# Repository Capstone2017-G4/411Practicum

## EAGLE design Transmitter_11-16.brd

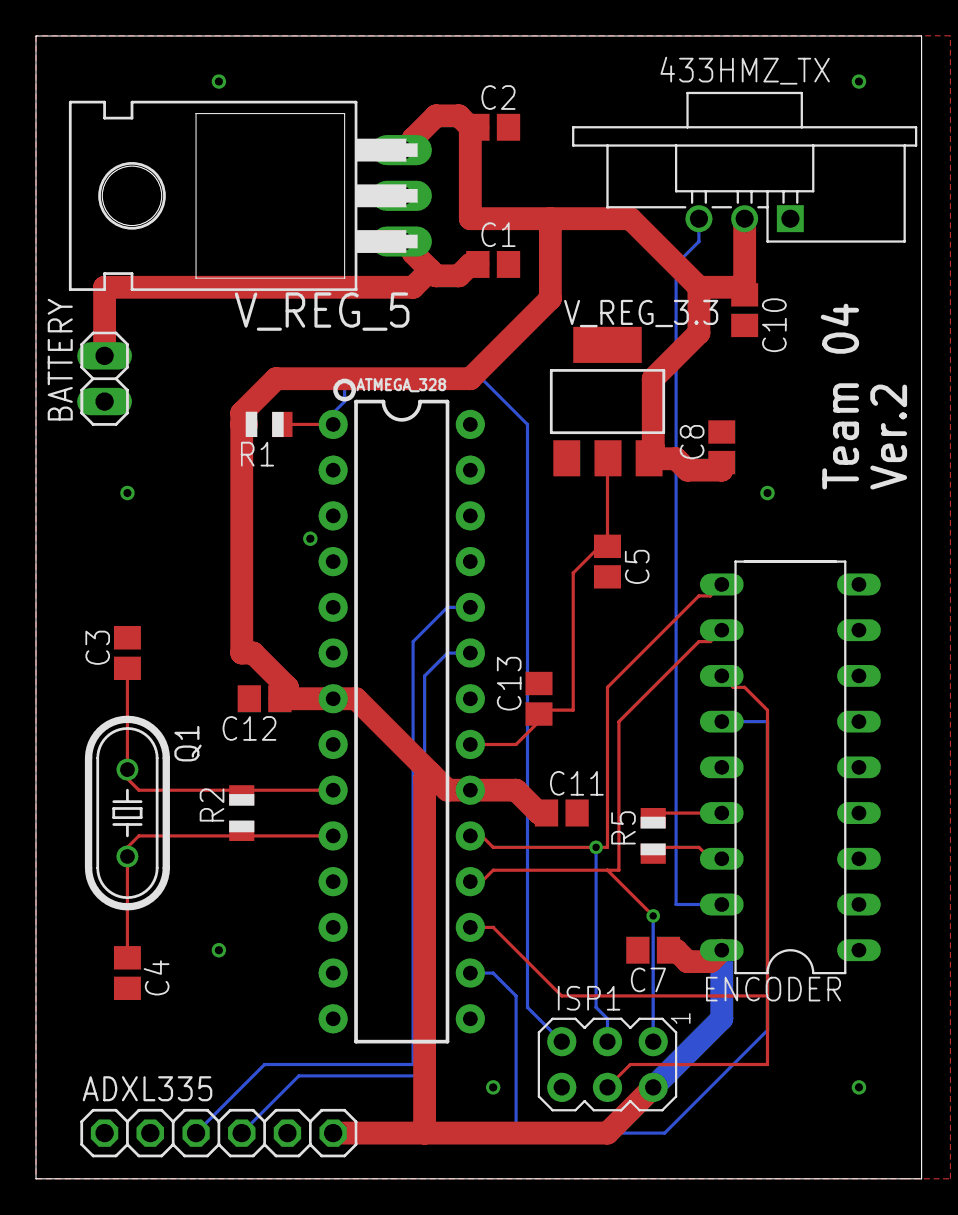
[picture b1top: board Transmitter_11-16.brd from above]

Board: 2 copper layers, 49.2 x 63.5 mm, 23 parts (0 on the bottom side), 16 nets.

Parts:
433HMZ_TX: WIRELESS-XY-FST#V
ADXL335: 1X06
ATMEGA_328: 328P; DIP28
BATTERY: 1X02
C1, C2, C5, C8: 10u; C0805
C3, C4: 22p; C0805
C7, C10, C11, C12, C13: 0.1u; C0805
ENCODER: HT12E"; 18-DIP-A
ISP1: AVRISP-6; AVRISP
Q1: 16MHz; HC49/S
R1: 10k; R0805
R2: 1M; R0805
R5: 750K; R0805
V_REG_3.3: REG1117; SOT223
V_REG_5: 7805T; TO220H

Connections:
+5V: 433HMZ_TX.2, ADXL335.6, ATMEGA_328.7, ATMEGA_328.20, C2.1, C7.1, C8.1, C10.1, C11.1, C12.1, ENCODER.18, ISP1.2, R1.2, V_REG_3.3.3, V_REG_5.3
AD08: ATMEGA_328.19, ENCODER.10, ISP1.3
GND: 433HMZ_TX.1, ADXL335.5, ATMEGA_328.8, ATMEGA_328.22, BATTERY.1, C1.2, C2.2, C3.2, C4.2, C5.2, C7.2, C8.2, C10.2, C11.2, C12.2, C13.2, ENCODER.1, ENCODER.2, ENCODER.3, ENCODER.4, ENCODER.5, ENCODER.6, ENCODER.7, ENCODER.8, ENCODER.9, ENCODER.14, ISP1.6, V_REG_3.3.1, V_REG_5.2
unnamed: ATMEGA_328.9, C3.1, Q1.1, R2.2
unnamed: ATMEGA_328.18, ENCODER.11, ISP1.1
unnamed: ADXL335.4, ATMEGA_328.23
unnamed: ATMEGA_328.10, C4.1, Q1.2, R2.1
unnamed: ENCODER.16, R5.1
unnamed: ENCODER.15, R5.2
unnamed: 433HMZ_TX.3, ENCODER.17
unnamed: ATMEGA_328.16, ENCODER.13
unnamed: ATMEGA_328.17, ENCODER.12, ISP1.4
unnamed: ADXL335.3, ATMEGA_328.24
unnamed: ATMEGA_328.21, C5.1, C13.1, V_REG_3.3.2
RESET: ATMEGA_328.1, ISP1.5, R1.1
VCC: BATTERY.2, C1.1, V_REG_5.1

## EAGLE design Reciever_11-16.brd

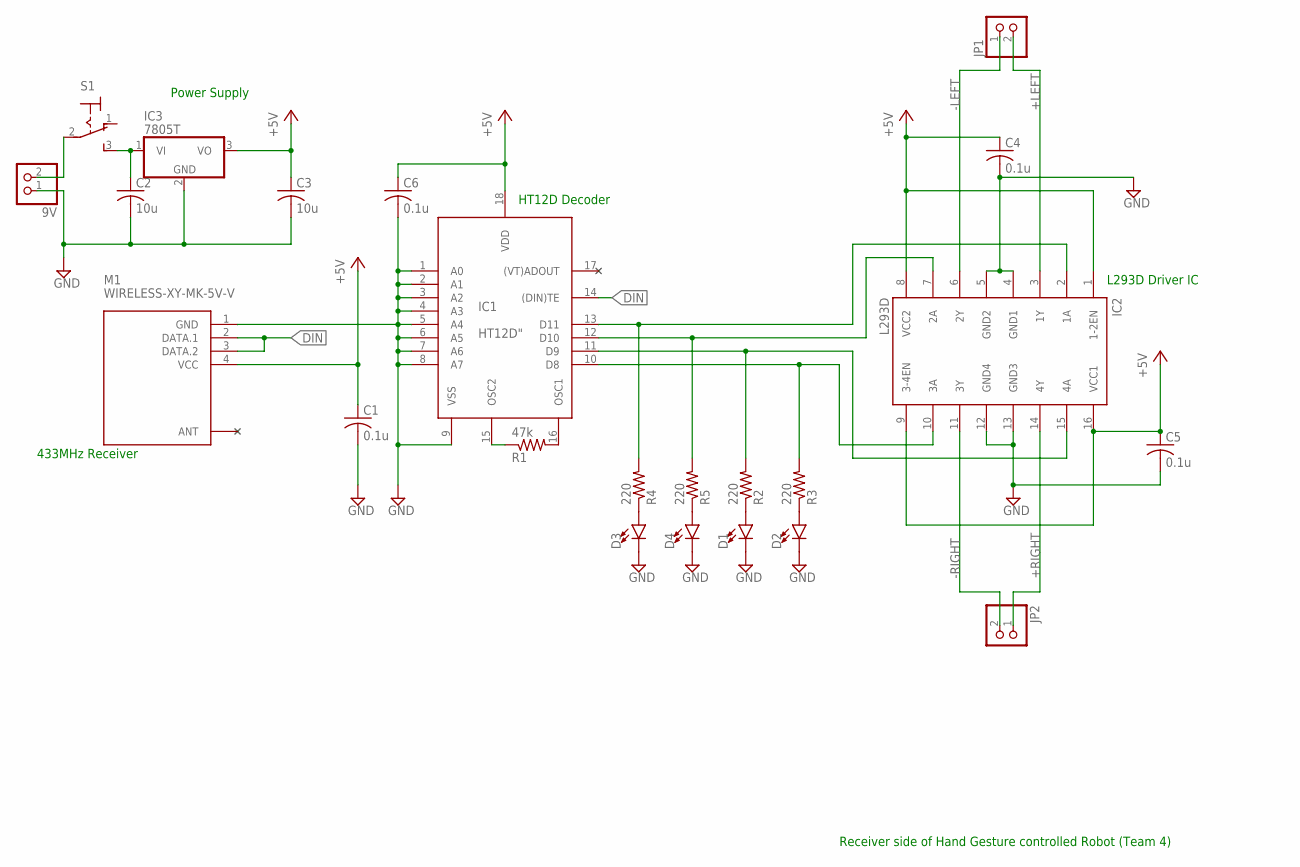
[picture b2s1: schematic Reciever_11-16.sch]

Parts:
9V: PINHD-1X2; 1X02
C1, C4, C5, C6: 0.1u; C0805
C2, C3: 10u; C0805
D1, D2, D3, D4: LED3MM; LED_3MM
IC1: HT12D"; 18-DIP-A
IC2: L293D; DIL16
IC3: 7805T; TO220H
JP1, JP2: PINHD-1X2; 1X02
M1: WIRELESS-XY-MK-5V-V; WIRELESS-XY-MK-5V#V
R1: 47k; R0805
R2, R3, R4, R5: 220; R0805
S1: M9040P

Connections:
+5V: C1.1, C3.1, C4.1, C5.1, C6.1, IC1.18 (VDD), IC2.1 (1-2EN), IC2.8 (VCC2), IC2.9 (3-4EN), IC2.16 (VCC1), IC3.3 (VO), M1.4 (VCC)
+LEFT: IC2.3 (1Y), JP1.2; also elsewhere on the board
+RIGHT: IC2.14 (4Y), JP2.1; also elsewhere on the board
-LEFT: IC2.6 (2Y), JP1.1; also elsewhere on the board
-RIGHT: IC2.11 (3Y), JP2.2; also elsewhere on the board
DIN: IC1.14 ((DIN)TE), M1.2 (DATA.1), M1.3 (DATA.2)
GND: 9V.1, C1.2, C2.2, C3.2, C4.2, C5.2, C6.2, D1.K (C), D2.K (C), D3.K (C), D4.K (C), IC1.1 (A0), IC1.2 (A1), IC1.3 (A2), IC1.4 (A3), IC1.5 (A4), IC1.6 (A5), IC1.7 (A6), IC1.8 (A7), IC1.9 (VSS), IC2.4 (GND1), IC2.5 (GND2), IC2.12 (GND4), IC2.13 (GND3), IC3.2 (GND), M1.1 (GND)
unnamed: IC1.16 (OSC1), R1.2
unnamed: IC1.10 (D8), IC2.10 (3A), R3.2
unnamed: IC1.15 (OSC2), R1.1
unnamed: D1.A, R2.1
unnamed: IC1.11 (D9), IC2.15 (4A), R2.2
unnamed: IC1.12 (D10), IC2.7 (2A), R5.2
unnamed: IC1.13 (D11), IC2.2 (1A), R4.2
unnamed: 9V.2, S1.2
unnamed: D2.A, R3.1
unnamed: D3.A, R4.1
unnamed: D4.A, R5.1
unnamed: C2.1, IC3.1 (VI), S1.3 (S)

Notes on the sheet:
HT12D Decoder
L293D Driver IC
433MHz Receiver
Receiver side of Hand Gesture controlled Robot (Team 4)
Power Supply

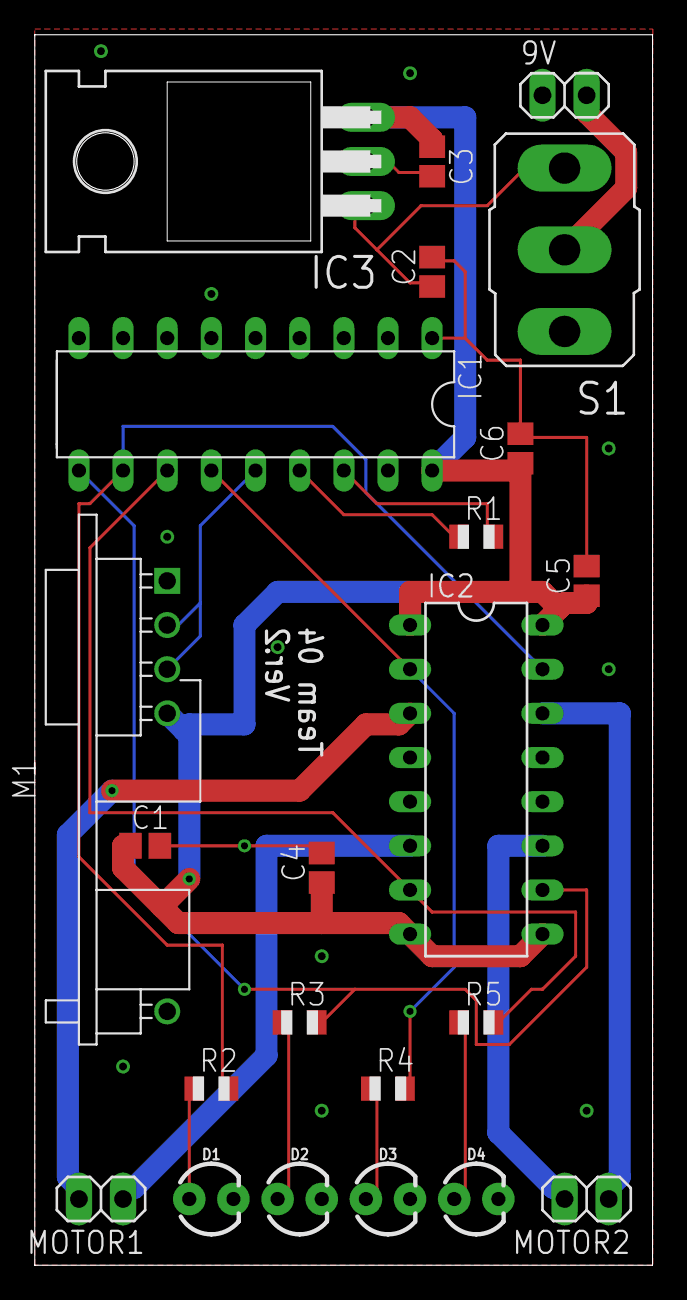
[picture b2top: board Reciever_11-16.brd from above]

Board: 2 copper layers, 35.5 x 70.8 mm, 23 parts (0 on the bottom side), 19 nets.

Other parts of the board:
MOTOR1, MOTOR2: 1X02

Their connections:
+LEFT: MOTOR1.2; also elsewhere on the board
+RIGHT: MOTOR2.1; also elsewhere on the board
-LEFT: MOTOR1.1; also elsewhere on the board
-RIGHT: MOTOR2.2; also elsewhere on the board

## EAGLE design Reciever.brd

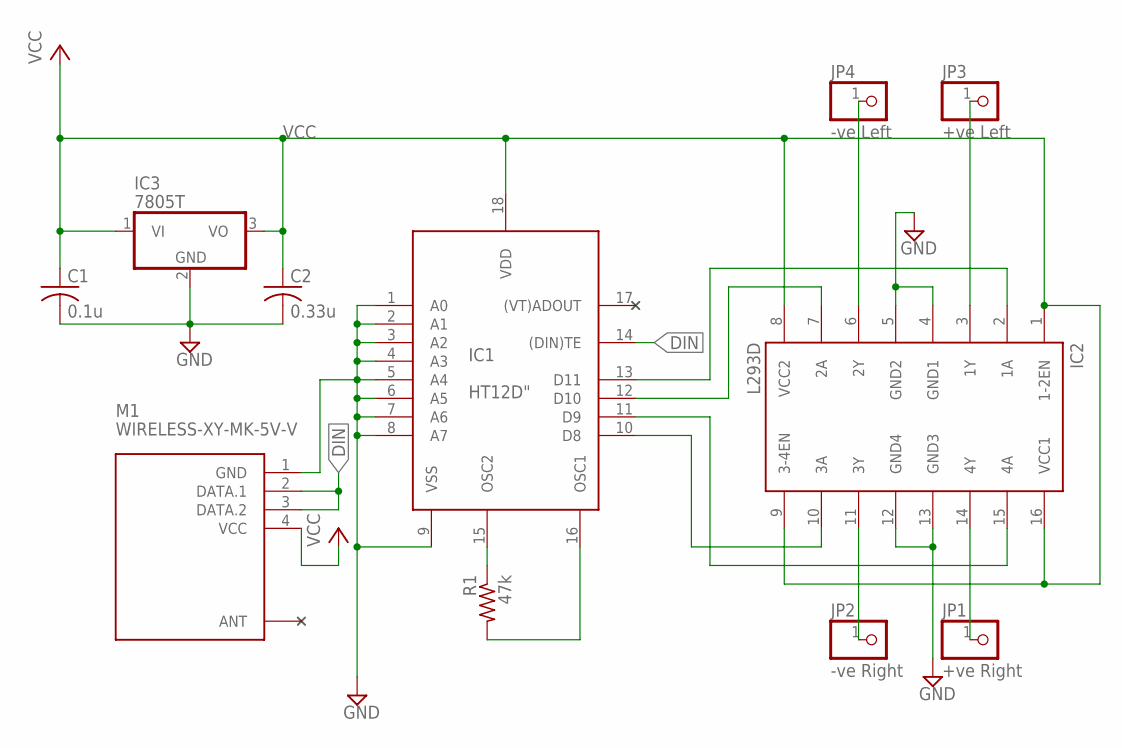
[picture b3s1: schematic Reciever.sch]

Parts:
C1: 0.1u; C0805
C2: 0.33u; C0805
IC1: HT12D"; 18-DIP-A
IC2: L293D; DIL16
IC3: 7805T; TO220H
JP1: +ve Right; 1X01
JP2: -ve Right; 1X01
JP3: +ve Left; 1X01
JP4: -ve Left; 1X01
M1: WIRELESS-XY-MK-5V-V; WIRELESS-XY-MK-5V#V
R1: 47k; R0805

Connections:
DIN: IC1.14 ((DIN)TE), M1.2 (DATA.1), M1.3 (DATA.2)
GND: C1.2, C2.2, IC1.1 (A0), IC1.2 (A1), IC1.3 (A2), IC1.4 (A3), IC1.5 (A4), IC1.6 (A5), IC1.7 (A6), IC1.8 (A7), IC1.9 (VSS), IC2.4 (GND1), IC2.5 (GND2), IC2.12 (GND4), IC2.13 (GND3), IC3.2 (GND), M1.1 (GND)
unnamed: IC2.6 (2Y), JP4.1
unnamed: IC1.10 (D8), IC2.10 (3A)
unnamed: IC1.15 (OSC2), R1.1
unnamed: IC1.16 (OSC1), R1.2
unnamed: IC1.11 (D9), IC2.15 (4A)
unnamed: IC1.12 (D10), IC2.7 (2A)
unnamed: IC1.13 (D11), IC2.2 (1A)
unnamed: IC2.3 (1Y), JP3.1
unnamed: IC2.11 (3Y), JP2.1
unnamed: IC2.14 (4Y), JP1.1
VCC: C1.1, C2.1, IC1.18 (VDD), IC2.1 (1-2EN), IC2.8 (VCC2), IC2.9 (3-4EN), IC2.16 (VCC1), IC3.1 (VI), IC3.3 (VO), M1.4 (VCC)

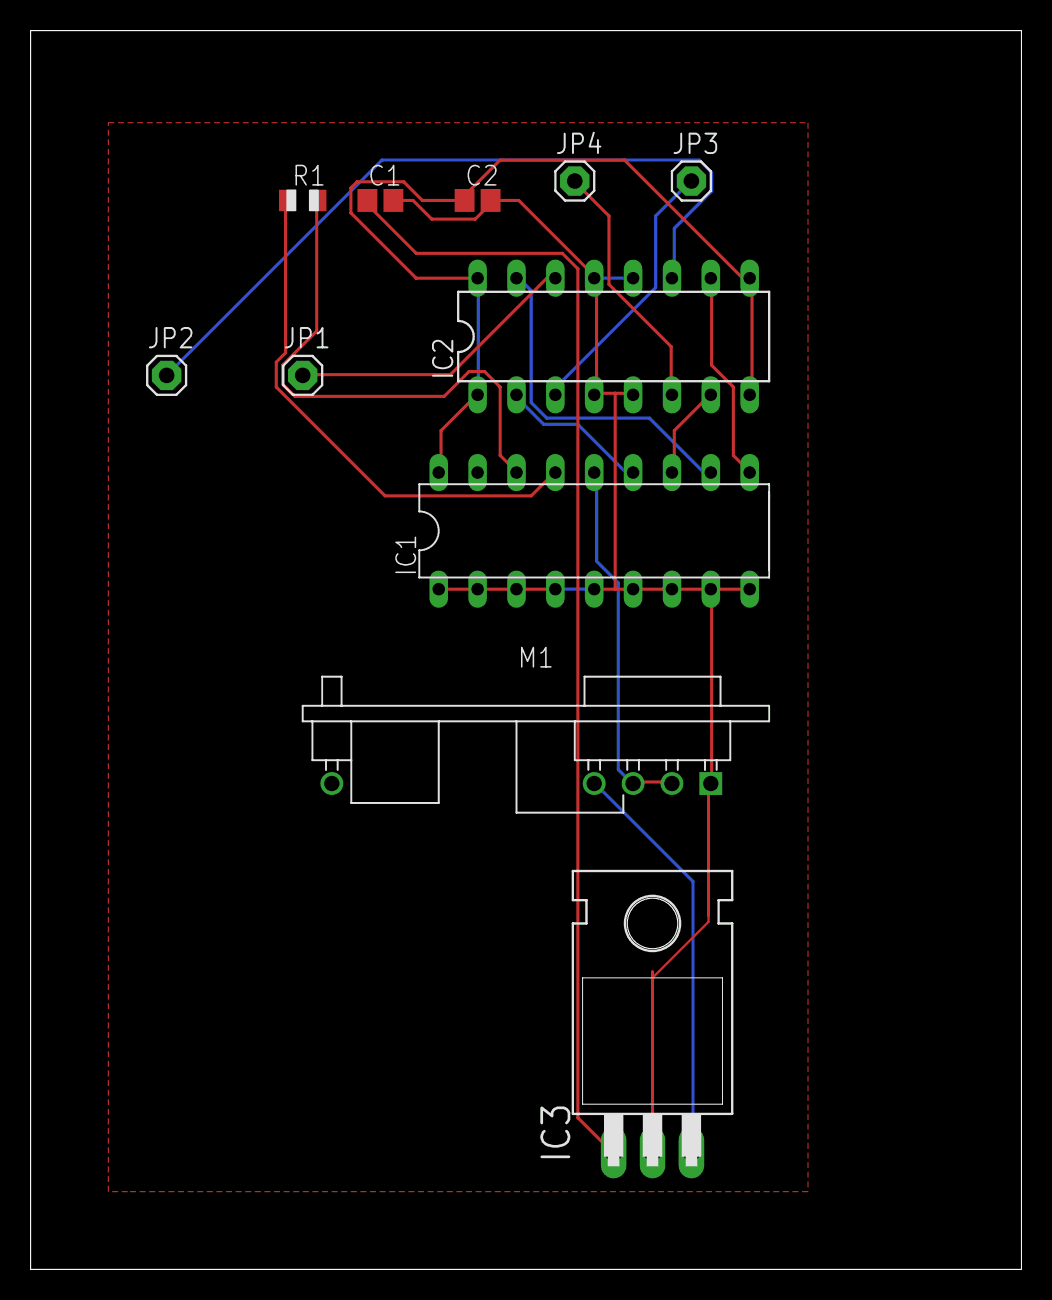
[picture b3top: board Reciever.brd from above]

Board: 2 copper layers, 64.8 x 80.9 mm, 11 parts (0 on the bottom side), 13 nets.

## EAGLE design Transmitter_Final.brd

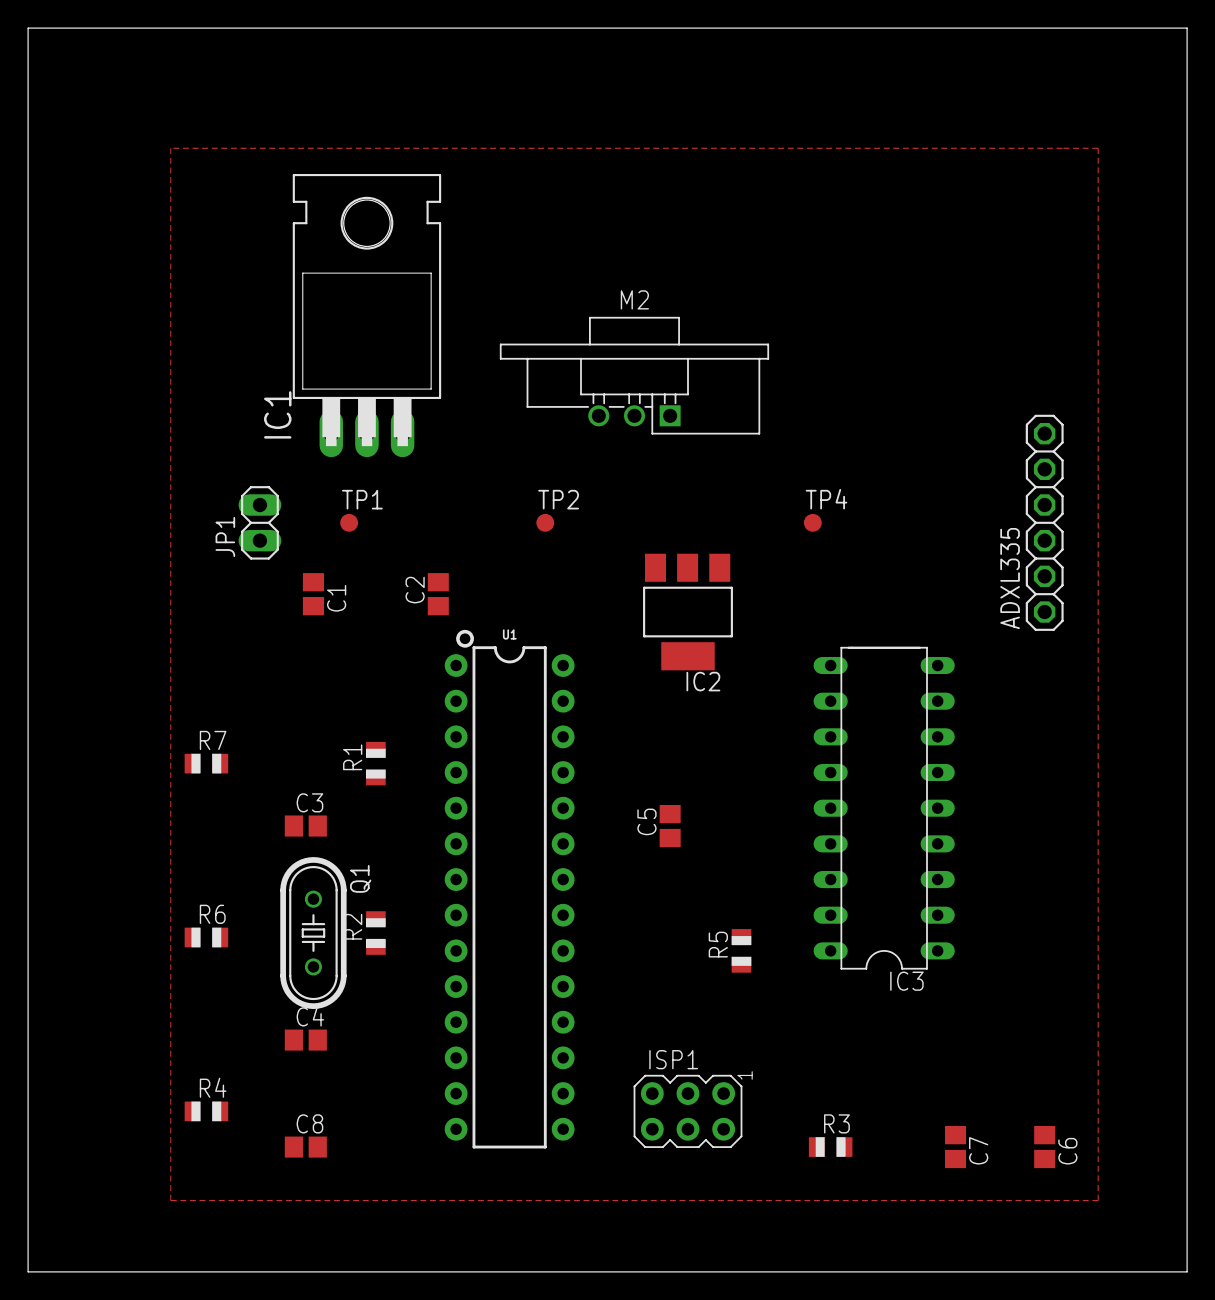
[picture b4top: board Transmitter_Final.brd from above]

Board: 2 copper layers, 82.5 x 88.6 mm, 27 parts (0 on the bottom side), 18 nets, no tracks yet.

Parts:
ADXL335: 1X06
C1, C2, C6, C7, C8: 0.1u; C0805
C3, C4: 22p; C0805
C5: 10u; C0805
IC1: 7805T; TO220H
IC2: REG1117; SOT223
IC3: HT12E"; 18-DIP-A
ISP1: AVRISP-6; AVRISP
JP1: 1X02
M2: WIRELESS-XY-FST#V
Q1: 16MHz; HC49/S
R1, R3, R4, R6, R7: 10k; R0805
R2: 1M; R0805
R5: 750K; R0805
TP1, TP2, TP4: TPB1,27; B1,27
U1: 328P; DIP28

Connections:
+5V: ADXL335.6, C2.1, C6.1, C7.1, IC1.3, M2.2, R1.2, R3.1, R4.2, R6.1, R6.2, R7.1, U1.7, U1.20
AD08: IC3.10, ISP1.3, U1.19
AREF: C5.1, IC2.2, TP2.TP, U1.21
unnamed: C3.1, Q1.1, R2.2, U1.9
unnamed: IC3.11, ISP1.1, U1.18
unnamed: ADXL335.4, U1.23
unnamed: C4.1, Q1.2, R2.1, U1.10
unnamed: IC3.16, R5.1
unnamed: IC3.15, R5.2
unnamed: ISP1.2, R3.2
unnamed: IC3.13, U1.16
unnamed: IC3.12, ISP1.4, U1.17
unnamed: IC2.3, R7.2
unnamed: ADXL335.3, U1.24
unnamed: IC3.17, M2.3, TP4.TP
unnamed: ADXL335.5, C1.2, C2.2, C3.2, C4.2, C5.2, C6.2, C7.2, C8.1, C8.2, IC1.2, IC2.1, IC3.1, IC3.2, IC3.3, IC3.4, IC3.5, IC3.6, IC3.7, IC3.8, IC3.9, IC3.14, IC3.18, ISP1.6, JP1.1, M2.1, R4.1, TP1.TP, U1.8, U1.22
RESET: ISP1.5, R1.1, U1.1
VCC: C1.1, IC1.1, JP1.2

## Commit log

2017-11-16 new edits 11-15
2017-11-16 16/11 Receiver file: need to check 16th 8am
2017-11-16 16/11 transmitter file: need to check 16th 8am
2017-11-16 Final Schematic and Board files for OSHPark
2017-11-30 prototype code that is working
2017-11-30 removed final code file
2017-11-30 prototype code
2017-11-30 rev1 of prototype test code
2017-12-07 Final Presentation

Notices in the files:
parts and their libraries:
diy-modules: Released under the Creative Commons Attribution 4.0 International License: http://creativecommons.org/licenses/by/4.0
SparkFun-LED: Licensing: Creative Commons ShareAlike 4.0 International - https://creativecommons.org/licenses/by-sa/4.0
